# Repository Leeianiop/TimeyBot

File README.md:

# TimeyBot

## A cute Time tracker, Base functions include:
Stopwatch,
Timer,
Local Time,
Calendar reminder,
Alarm,
Music Player,
Pomodoro Tracker.
## Why Timey

It began when I was studying for exams; I always needed a study tool that was a time tracker and doubled as an audio player.  
Sure, there were phone apps to do so, but i kept finding myself scrolling whenever I go check on it.  
You could say I had been planing to make Timey for a long time  
It features all-in-one functions and can be built on to add your own Songs, Functions, Design and more.  
I made it specifically so that it doubles as a study partner, with time tracking and task reminder features and no distractions from other apps.    
## BOM

| Component | Description | Unit Price | Qty | Total |
|------------|------------|------------|-----|--------|
| ESP32 Dev Board (Micro USB) | Microcontroller | $6.03 | 1 | $6.03 |
| 128x64 1.3" OLED Display (I2C) | UI Display | $5.49 | 1 | $5.49 |
| 4Ω Speaker | Playing Music and Alarms | $3.63 | 1 | $3.63 |
| MAX98357 Amplifier | Amplify Sound | $3.27 | 1 | $3.27 |
| Jumper Wires (Female-Female) | Connect the Circuit | $1.48 | 1 | $1.48 |
| USB to Wires Cable | Power the Circuit | $1.75 | 1 | $1.75 |
| Push Button | Control the UI | $0.66 | 1 | $0.66 |
| Screw (10 pcs) | Locking in the PCB and components | $1.20 | 1 | $1.20 |
| Pin Header Female | Solder into PCB | $0.50 | 1 | $0.50 |
| DS3231 RTC module | Track local time offline | $2.21 | 1 | $2.21 |
| Pin Header Male (1x40) |Connecting components with PCB | $0.12 | 1 | $0.12 |
| 0805 SMD Ceramic Capacitor | Prevent brownout/ ESP crashes | $1.22 | 1 | $1.22 |
| Terminal Block 2p | To connect USB cable to esp | $0.12 | 1 | $0.12 |
| Hex Nut (M3) | To lock in button PCB and slider | $0.12 | 1 | $0.32 |

### Optional Storage Upgrade (For MP3 files)

| Component | Description | Price |
|------------|------------|--------|
| Micro SD Card | Store MP3 Files | $1.13 |
| Micro SD Card Reader | Connect to ESP32 | $0.50 |

### Estimated Total Cost

**$29.33 USD**   

STL files include: (TimeyBotMainCase), (TimeyBotSlider), (TimeyBotBackplate), (Extensions file>> (TimeyBot_eDog), (TimeyBot_eCat) )  
PCB files include: (TimeyBotPCB), (TimeyBotSCH)   

## How to Use?
The starting page will be the Local Time Mode. Click the button on top (HEAD) to scroll down the menu and select different modes:
- Music Player Mode - Listening  
- Time Track Mode - Timer, Stopwatch, Alarm, Calendar Reminder  
- Study Mode - Pomodoro & Music  
## Setting up
1. Print the STL files.  
2. Upload the IDE code into the ESP32, remember to install ESP Boards and Adafruit Libraries. 
3. Wire the components into the case as shown in the Wiring Diagram or Get the PCB board and connect according so.
4. PCB goes and RTC and SD and AMP go behind where they are labeled in the STL file :)  

Hope you like Mr Timey ;) 35 hours logged on this project (as of now)

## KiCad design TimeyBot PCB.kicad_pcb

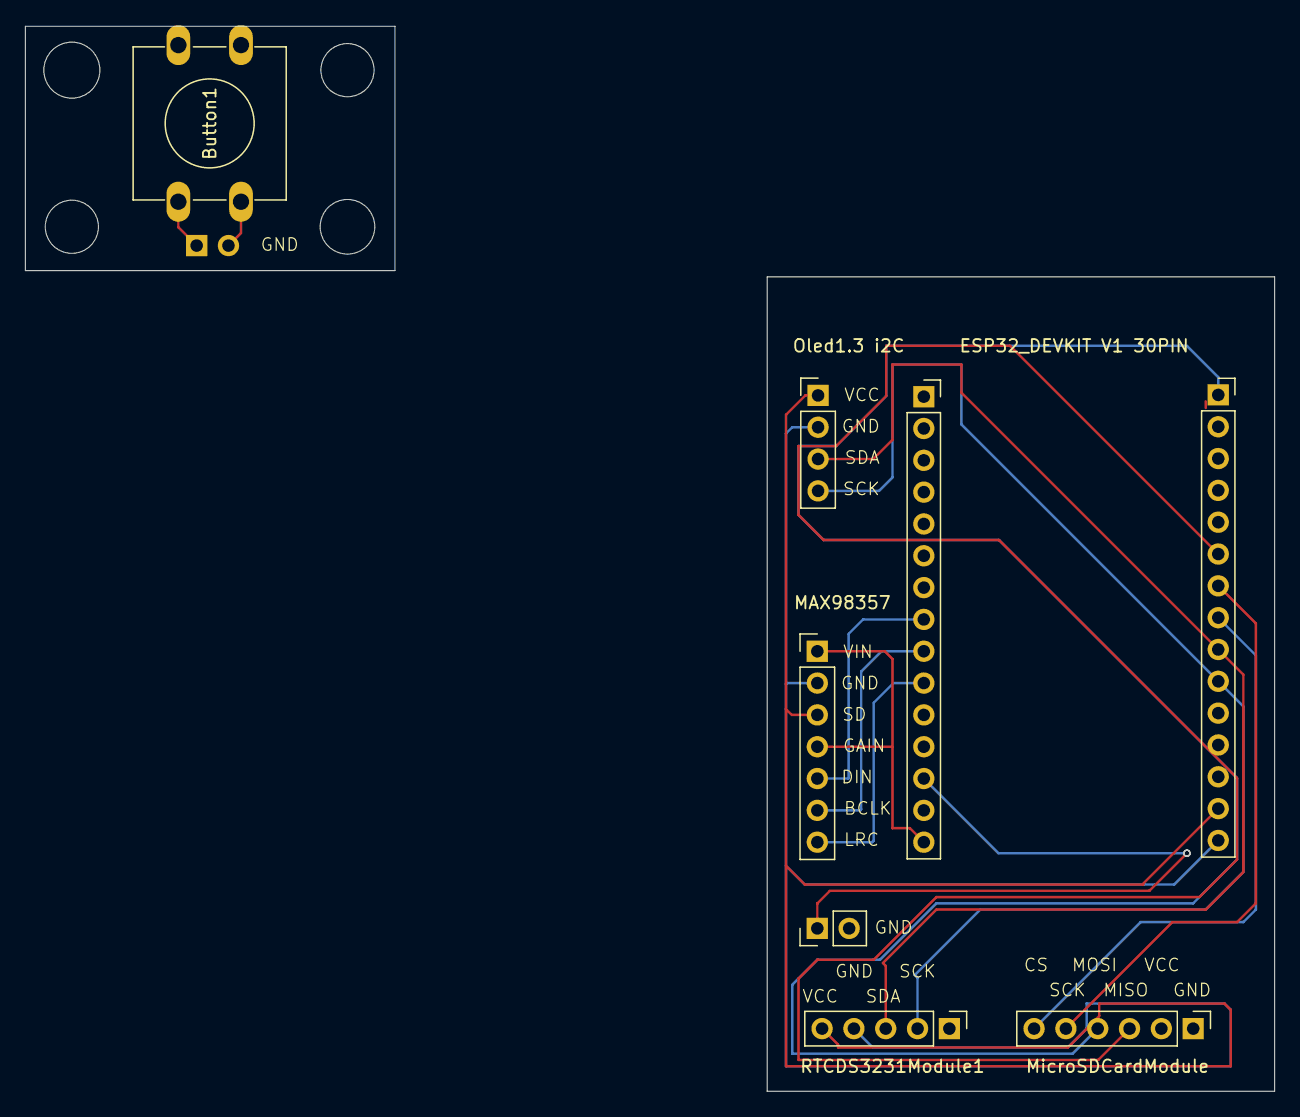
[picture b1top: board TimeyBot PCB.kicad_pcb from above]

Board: 2 copper layers, 99.7 x 85.0 mm, 9 parts (1 on the bottom side), 2 nets.

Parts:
Button1: SW_Push; SW_PUSH-12mm
Button2, Button3: Conn_01x02_Socket; PinHeader_1x02_P2.54mm_Vertical
ESP32_30PIN2, ESP32_DEVKIT V1 30PIN: Conn_01x15_Socket; PinSocket_1x15_P2.54mm_Vertical
MAX98357: Conn_01x07_Socket; PinHeader_1x07_P2.54mm_Vertical
MicroSDCardModule: Conn_01x06_Socket; PinHeader_1x06_P2.54mm_Vertical
Oled1.3 i2C: Conn_01x04_Socket; PinHeader_1x04_P2.54mm_Vertical
RTCDS3231Module1: Conn_01x05_Socket; PinHeader_1x05_P2.54mm_Vertical

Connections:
unnamed: Button1.2, Button3.1
unnamed: Button1.1, Button3.2

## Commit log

2026-06-02 Create README STUFF
2026-06-02 Rename Timey Bot.png to TimeyBot.png
2026-06-02 Rename Readme Timey.png to ReadmeTimey.png
2026-06-14 Create CAD
2026-06-14 Clarify wiring instructions in README
    Updated instructions for wiring components in the setup section.
2026-06-15 Rename TimeyBot PCB.kicad_pcb to TimeyBotPCB.kicad_pcb
2026-06-15 Rename ~TimeyBot PCB.kicad_pro.lck to ~TimeyBotPCB.kicad_pro.lck
2026-06-15 Rename TimeyBot SCH.kicad_sch to TimeyBotSCH.kicad_sch
2026-06-15 Rename TimeyBot PCB.kicad_pro to TimeyBotPCB.kicad_pro
2026-06-15 Rename TimeyBotMianCase.f3d to TimeyBotMainCase.f3d
